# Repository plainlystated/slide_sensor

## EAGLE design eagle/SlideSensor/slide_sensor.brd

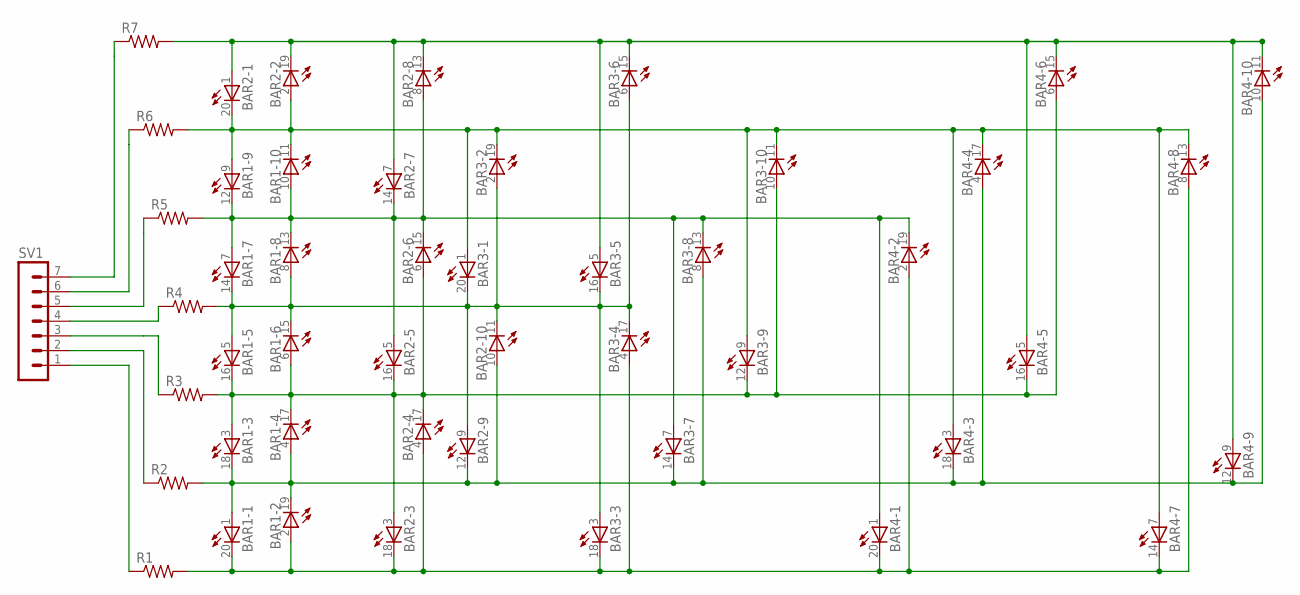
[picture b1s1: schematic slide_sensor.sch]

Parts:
BAR1, BAR2, BAR3, BAR4: LB10
R1, R2, R3, R4, R5, R6, R7: R-US_0207/7; 0207/7
SV1: MA07-1

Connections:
N$L1: BAR1.2 (A), BAR1.20 (C), BAR2.4 (A), BAR2.18 (C), BAR3.4 (A), BAR3.18 (C), BAR4.2 (A), BAR4.8 (A), BAR4.14 (C), BAR4.20 (C), R1.2
N$L2: BAR1.1 (A), BAR1.4 (A), BAR1.18 (C), BAR1.19 (C), BAR2.10 (A), BAR2.12 (C), BAR3.8 (A), BAR3.14 (C), BAR4.4 (A), BAR4.10 (A), BAR4.12 (C), BAR4.18 (C), R2.2
N$L3: BAR1.3 (A), BAR1.6 (A), BAR1.16 (C), BAR1.17 (C), BAR2.3 (A), BAR2.6 (A), BAR2.16 (C), BAR2.17 (C), BAR3.10 (A), BAR3.12 (C), BAR4.6 (A), BAR4.16 (C), R3.2
N$L4: BAR1.5 (A), BAR1.8 (A), BAR1.14 (C), BAR1.15 (C), BAR2.9 (A), BAR2.11 (C), BAR3.2 (A), BAR3.3 (A), BAR3.6 (A), BAR3.16 (C), BAR3.17 (C), BAR3.20 (C), R4.2
N$L5: BAR1.7 (A), BAR1.10 (A), BAR1.12 (C), BAR1.13 (C), BAR2.5 (A), BAR2.8 (A), BAR2.14 (C), BAR2.15 (C), BAR3.7 (A), BAR3.13 (C), BAR4.1 (A), BAR4.19 (C), R5.2
N$L6: BAR1.9 (A), BAR1.11 (C), BAR2.2 (A), BAR2.20 (C), BAR3.1 (A), BAR3.9 (A), BAR3.11 (C), BAR3.19 (C), BAR4.3 (A), BAR4.7 (A), BAR4.13 (C), BAR4.17 (C), R6.2
N$L7: BAR2.1 (A), BAR2.7 (A), BAR2.13 (C), BAR2.19 (C), BAR3.5 (A), BAR3.15 (C), BAR4.5 (A), BAR4.9 (A), BAR4.11 (C), BAR4.15 (C), R7.2
N$P1: R1.1, SV1.1
N$P2: R2.1, SV1.2
N$P3: R3.1, SV1.3
N$P4: R4.1, SV1.4
N$P5: R5.1, SV1.5
N$P6: R6.1, SV1.6
N$P7: R7.1, SV1.7

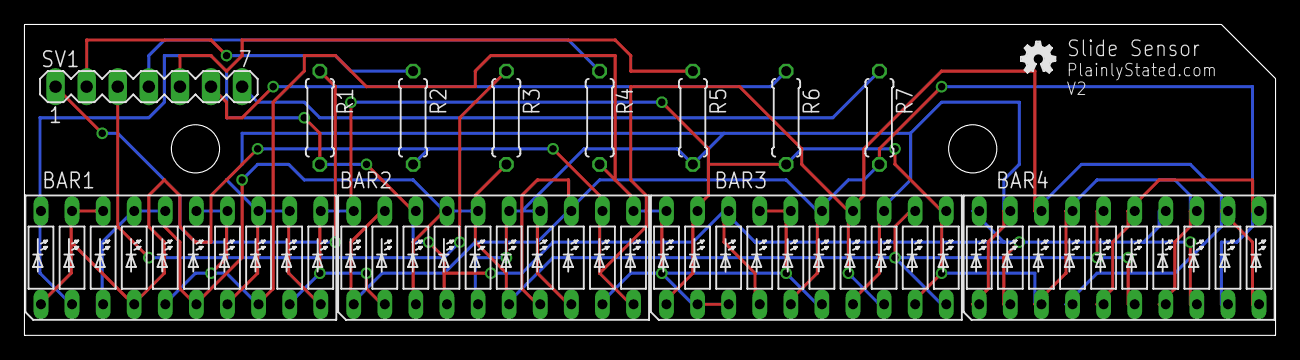
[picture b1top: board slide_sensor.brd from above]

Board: 2 copper layers, 102.2 x 25.4 mm, 13 parts (0 on the bottom side), 14 nets.

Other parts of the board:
U$1: OSHW_FILLX100_NOTEXT

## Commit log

2013-06-16 version 1
2013-07-05 v2 - fix bad schematic
